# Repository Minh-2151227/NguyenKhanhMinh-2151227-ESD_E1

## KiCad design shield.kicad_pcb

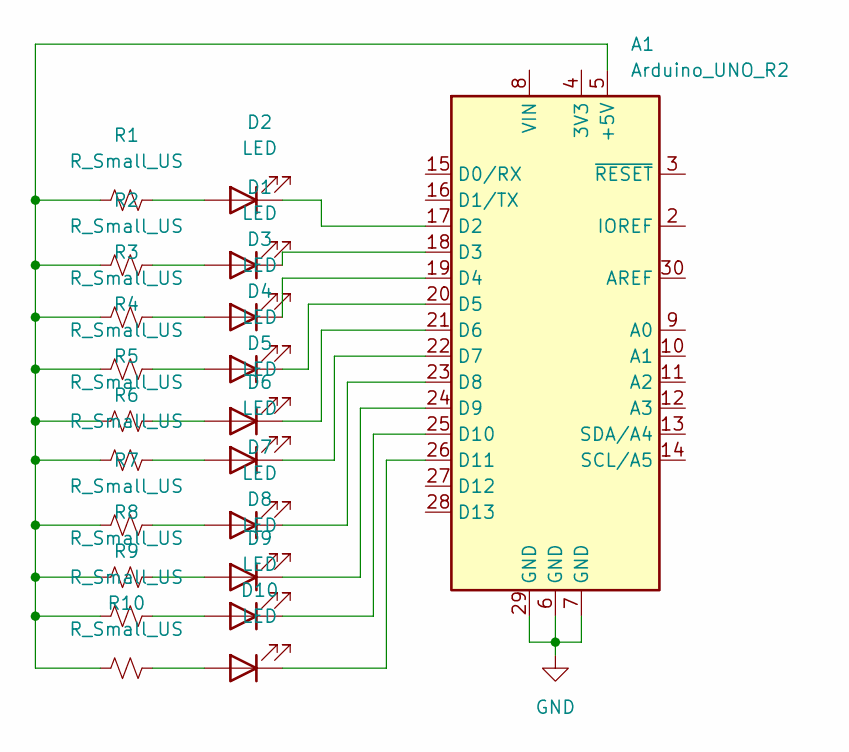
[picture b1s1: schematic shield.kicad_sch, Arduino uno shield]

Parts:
A1: Arduino_UNO_R2
D1, D2, D3, D4, D5, D6, D7, D8, D9, D10: LED; LED_0805_2012Metric
R1, R2, R3, R4, R5, R6, R7, R8, R9, R10: R_Small_US; R_0603_1608Metric

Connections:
GND: A1.6 (GND), A1.7 (GND), A1.29 (GND)
unnamed: A1.5 (+5V), R1.1, R2.1, R3.1, R4.1, R5.1, R6.1, R7.1, R8.1, R9.1, R10.1
unnamed: A1.17 (D2), D2.1 (K)
unnamed: A1.18 (D3), D1.1 (K)
unnamed: A1.19 (D4), D3.1 (K)
unnamed: A1.20 (D5), D4.1 (K)
unnamed: A1.21 (D6), D5.1 (K)
unnamed: A1.22 (D7), D6.1 (K)
unnamed: A1.23 (D8), D7.1 (K)
unnamed: A1.24 (D9), D8.1 (K)
unnamed: A1.25 (D10), D9.1 (K)
unnamed: A1.26 (D11), D10.1 (K)
unnamed: D1.2 (A), R2.2
unnamed: D2.2 (A), R1.2
unnamed: D3.2 (A), R3.2
unnamed: D4.2 (A), R4.2
unnamed: D5.2 (A), R5.2
unnamed: D6.2 (A), R6.2
unnamed: D7.2 (A), R7.2
unnamed: D8.2 (A), R8.2
unnamed: D9.2 (A), R9.2
unnamed: D10.2 (A), R10.2

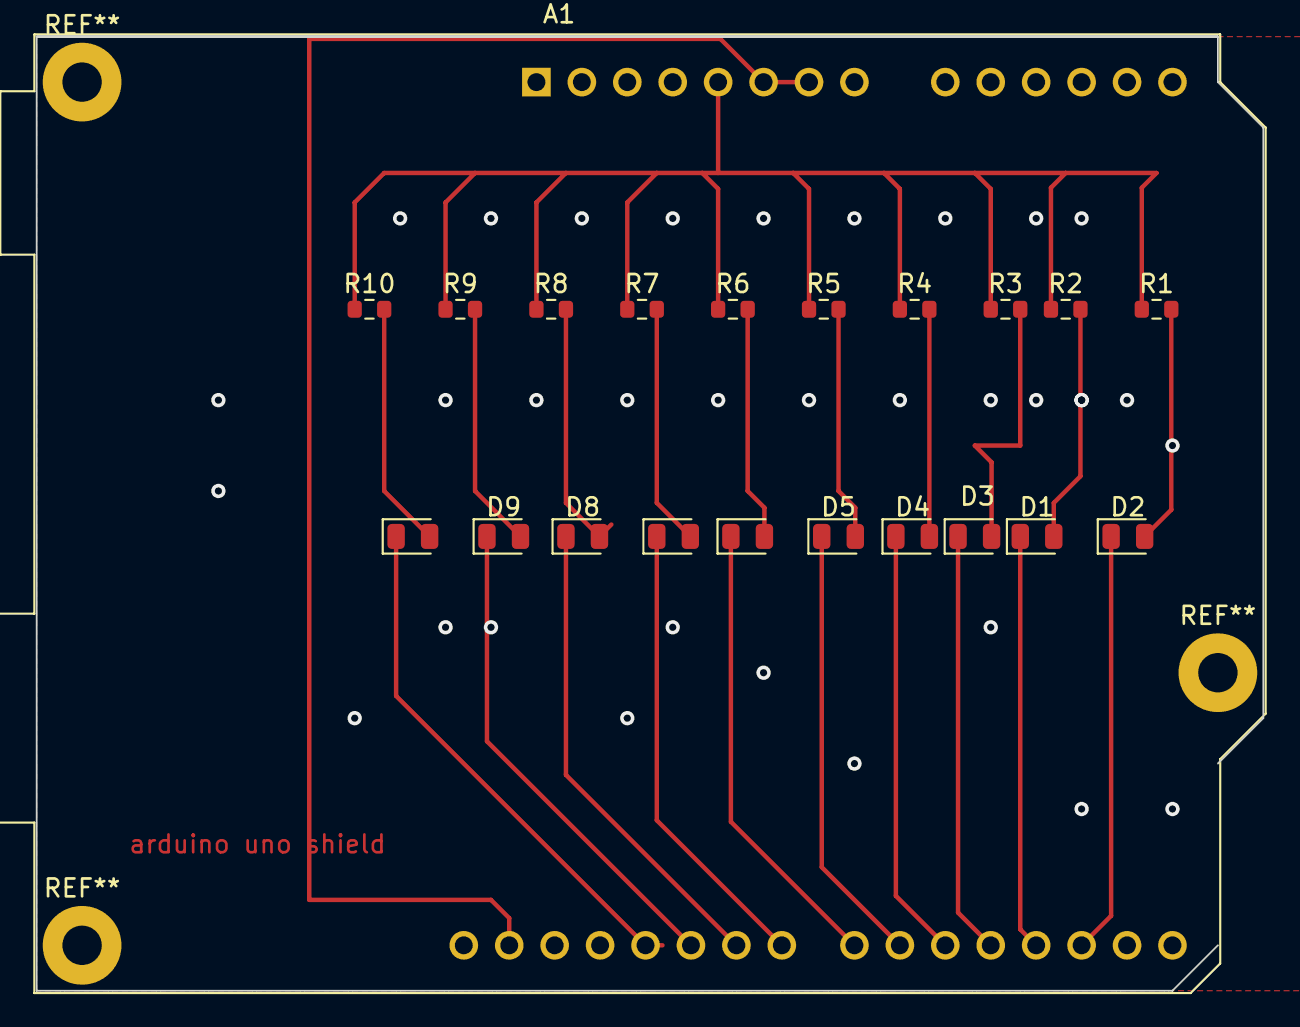
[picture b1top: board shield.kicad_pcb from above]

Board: 2 copper layers, 68.6 x 53.3 mm, 21 parts (0 on the bottom side), 22 nets.
